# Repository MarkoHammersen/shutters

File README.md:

# ESP32 Shutter Control System
This project implements a **ESP32-based shutter control system** designed for controlling shutter motors via relays, with clear separation between hardware abstraction and business logic.
The system combines **ESP32**, **Microchip MCP23017 I/O expanders**, and **ULN2003A Darlington arrays**, and is implemented in **C++ using PlatformIO with the Arduino framework**.

---

## System Overview
The shutter system consists of:

* An **ESP32** as the central controller
* **MCP23017 I/O expanders** for scalable digital input and output via I²C
* **ULN2003A Darlington transistor arrays** for driving relay coils
* A dedicated **external 5 V power supply** for stable I/O operation

All safety-relevant design aspects (galvanic separation, flyback protection, low coil current) are explicitly addressed in the extern hardware design, which is not part of the schematics attached.

---

## Hardware Architecture

### Inputs (Buttons / Wall Switches)

* Digital inputs are handled by an **MCP23017 configured as input expander**
* Button **press and release events** are captured
* Each input event triggers a **hardware interrupt**
* The interrupt line is connected to the ESP32
* Upon interrupt, the ESP32:

  1. Starts an I²C transaction
  2. Reads the MCP23017 input registers
  3. Determines the exact event (press or release)

This approach ensures:

* Low latency
* Minimal polling
* Efficient I²C bus usage

---

### Outputs (Shutter Actuation)

* Outputs are handled by a second **MCP23017 configured as output expander**
* Output states are sent from the ESP32 via **I²C**
* MCP23017 outputs drive **ULN2003A Darlington arrays**
* The Darlington arrays drive the **relay coils**

#### Relay Driving

* Relay coil current is low enough to be **safely driven by ULN2003A**
* **Flyback diodes** are mounted directly at the relay coils
* This protects the Darlington arrays and improves EMC robustness

> ⚠️ **Note:** Mains voltage must only be handled by qualified personnel.
---

### Power Supply

* All MCP23017 inputs and outputs are powered by a **stable external 5 V supply**
* This ensures:

  * Reliable logic levels
  * Noise immunity
  * Stable operation independent of ESP32 load conditions

---

## Software Architecture

The firmware is written in **C++** and built using:

* **PlatformIO**
* **Arduino framework**
* **ESP32 target**

The software is cleanly structured into three main layers using dedicated FreeRTOS tasks. The communication between these tasks are done via message queues:

### 1. Sensors

* Abstraction of all input devices
* MCP23017 input handling
* Interrupt processing
* Debouncing and event detection (press / release)

### 2. Actuators

* Abstraction of all output devices
* MCP23017 output handling
* Relay control logic
* Hardware-independent actuator interface

### 3. Shutter Business Logic

* High-level shutter control logic
* Direction handling (up / down)
* Timing and safety constraints
* Mutual exclusion of motor directions

#### State Machine

The business logic is implemented using a **state machine** based on:

👉 **Quantum Leaps – State-Oriented Programming**
[https://github.com/QuantumLeaps/State-Oriented-Programming](https://github.com/QuantumLeaps/State-Oriented-Programming)

This provides:

* Explicit, deterministic state handling
* Clear separation of states and events
* Improved maintainability and testability
* Robust behavior for asynchronous events (buttons, interrupts)

---

## Documentation & Schematics

* Hardware schematics are included in the repository

---

## Key Features

* ESP32-based central control
* Interrupt-driven input handling
* Scalable I/O via MCP23017
* Safe relay driving using ULN2003A
* Clear separation of concerns in software
* State-machine-driven business logic

---
### ⚠️ WARNING

This project uses electromechanical actuators.
Improper handling can result in serious injury, fire, or death.

This project is provided for educational and experimental purposes only.
The author assumes no liability for any damage, injury, or loss resulting
from the use, misuse, or modification of this hardware or software.

Only qualified personnel should work with mains voltage systems.

---
This project is not certified for commercial or residential use.
No compliance with CE, VDE, UL, or any other safety standard is claimed.
--
Use at your own risk!

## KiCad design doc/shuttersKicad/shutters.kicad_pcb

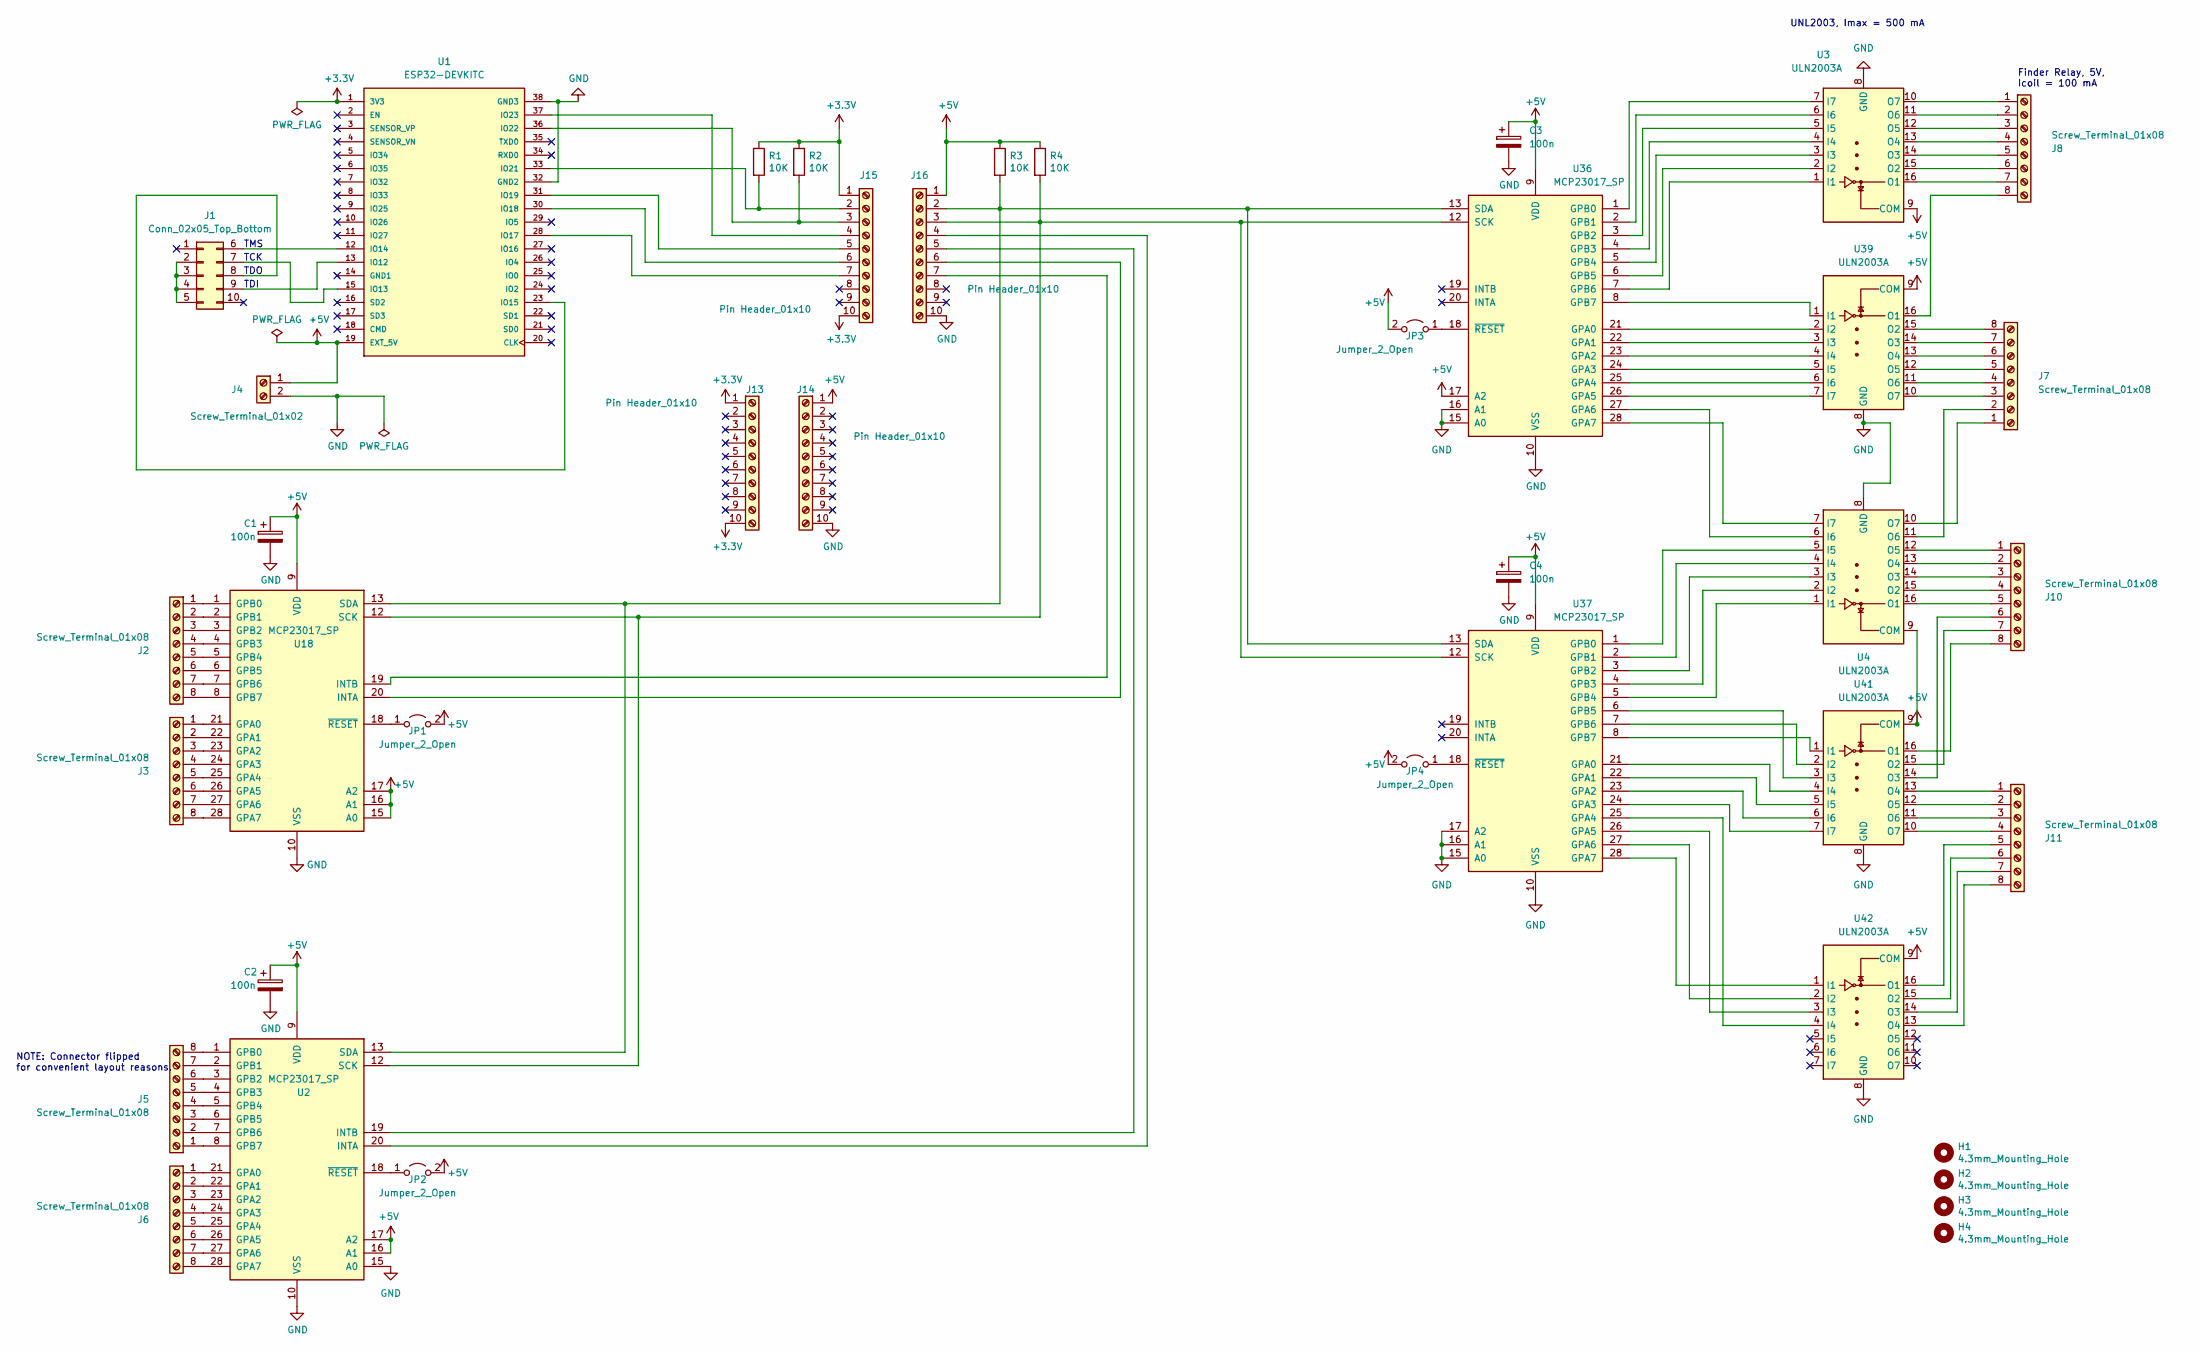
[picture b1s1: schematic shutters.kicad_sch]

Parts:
C1, C2, C3, C4: 100n; C_Rect_L7.0mm_W2.5mm_P5.00mm
H1, H2, H3, H4: 4.3mm_Mounting_Hole; MountingHole_4.3mm_M4
J1: Conn_02x05_Top_Bottom; PinHeader_2x05_P2.54mm_Vertical
J2, J3, J5, J6, J7, J8, J10, J11: Screw_Terminal_01x08; TerminalBlock_Phoenix_MKDS-1,5-8-5.08_1x08_P5.08mm_Horizont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
J4: Screw_Terminal_01x02; TerminalBlock_Phoenix_MKDS-1,5-2-5.08_1x02_P5.08mm_Horizont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
J13, J14, J15, J16: Pin Header_01x10; PinHeader_1x10_P2.54mm_Vertical
JP1, JP2, JP3, JP4: Jumper_2_Open; PinHeader_1x02_P2.54mm_Vertical
R1, R2, R3, R4: 10K; R_Axial_DIN0204_L3.6mm_D1.6mm_P5.08mm_Horizontal
U1: ESP32-DEVKITC; MODULE_ESP32-DEVKITC; PARTREV N/A
U2, U18, U36, U37: MCP23017_SP; DIP-28_W7.62mm
U3, U4, U39, U41, U42: ULN2003A; DIP-16_W7.62mm_Socket

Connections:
+3V3: J13.1, J13.10, J15.1, J15.10, R1.1, R2.1, U1.1 (3V3)
+5V: C1.1, C2.1, C3.1, C4.1, J4.1, J14.1, J16.1, JP1.2 (B), JP2.2 (B), JP3.2 (B), JP4.2 (B), R3.1, R4.1, U1.19 (EXT_5V), U2.9 (VDD), U2.16 (A1), U2.17 (A2), U3.9 (COM), U4.9 (COM), U18.9 (VDD), U18.15 (A0), U18.16 (A1), U18.17 (A2), U36.9 (VDD), U36.17 (A2), U37.9 (VDD), U39.9 (COM), U41.9 (COM), U42.9 (COM)
GND: C1.2, C2.2, C3.2, C4.2, J4.2, J14.10, J16.10, U1.32 (GND2), U1.38 (GND3), U2.10 (VSS), U2.15 (A0), U3.8 (GND), U4.8 (GND), U18.10 (VSS), U36.10 (VSS), U36.15 (A0), U36.16 (A1), U37.10 (VSS), U37.15 (A0), U37.16 (A1), U37.17 (A2), U39.8 (GND), U41.8 (GND), U42.8 (GND)
unnamed: J1.2, J1.3, J1.4, J1.5
unnamed: J1.6, U1.12 (IO14)
unnamed: J1.7, U1.15 (IO13)
unnamed: J1.8, U1.23 (IO15)
unnamed: J1.9, U1.13 (IO12)
unnamed: J2.1, U18.1 (GPB0)
unnamed: J2.2, U18.2 (GPB1)
unnamed: J2.3, U18.3 (GPB2)
unnamed: J2.4, U18.4 (GPB3)
unnamed: J2.5, U18.5 (GPB4)
unnamed: J2.6, U18.6 (GPB5)
unnamed: J2.7, U18.7 (GPB6)
unnamed: J2.8, U18.8 (GPB7)
unnamed: J3.1, U18.21 (GPA0)
unnamed: J3.2, U18.22 (GPA1)
unnamed: J3.3, U18.23 (GPA2)
unnamed: J3.4, U18.24 (GPA3)
unnamed: J3.5, U18.25 (GPA4)
unnamed: J3.6, U18.26 (GPA5)
unnamed: J3.7, U18.27 (GPA6)
unnamed: J3.8, U18.28 (GPA7)
unnamed: J5.1, U2.8 (GPB7)
unnamed: J5.2, U2.7 (GPB6)
unnamed: J5.3, U2.6 (GPB5)
unnamed: J5.4, U2.5 (GPB4)
unnamed: J5.5, U2.4 (GPB3)
unnamed: J5.6, U2.3 (GPB2)
unnamed: J5.7, U2.2 (GPB1)
unnamed: J5.8, U2.1 (GPB0)
unnamed: J6.1, U2.21 (GPA0)
unnamed: J6.2, U2.22 (GPA1)
unnamed: J6.3, U2.23 (GPA2)
unnamed: J6.4, U2.24 (GPA3)
unnamed: J6.5, U2.25 (GPA4)
unnamed: J6.6, U2.26 (GPA5)
unnamed: J6.7, U2.27 (GPA6)
unnamed: J6.8, U2.28 (GPA7)
unnamed: J7.1, U4.10 (O7)
unnamed: J7.2, U4.11 (O6)
unnamed: J7.3, U39.10 (O7)
unnamed: J7.4, U39.11 (O6)
unnamed: J7.5, U39.12 (O5)
unnamed: J7.6, U39.13 (O4)
unnamed: J7.7, U39.14 (O3)
unnamed: J7.8, U39.15 (O2)
unnamed: J8.1, U3.10 (O7)
unnamed: J8.2, U3.11 (O6)
unnamed: J8.3, U3.12 (O5)
unnamed: J8.4, U3.13 (O4)
unnamed: J8.5, U3.14 (O3)
unnamed: J8.6, U3.15 (O2)
unnamed: J8.7, U3.16 (O1)
unnamed: J8.8, U39.16 (O1)
unnamed: J10.1, U4.12 (O5)
unnamed: J10.2, U4.13 (O4)
unnamed: J10.3, U4.14 (O3)
unnamed: J10.4, U4.15 (O2)
unnamed: J10.5, U4.16 (O1)
unnamed: J10.6, U41.14 (O3)
unnamed: J10.7, U41.15 (O2)
unnamed: J10.8, U41.16 (O1)
unnamed: J11.1, U41.13 (O4)
unnamed: J11.2, U41.12 (O5)
unnamed: J11.3, U41.11 (O6)
unnamed: J11.4, U41.10 (O7)
unnamed: J11.5, U42.16 (O1)
unnamed: J11.6, U42.15 (O2)
unnamed: J11.7, U42.14 (O3)
unnamed: J11.8, U42.13 (O4)
unnamed: J15.2, R1.2, U1.33 (IO21)
unnamed: J15.3, R2.2, U1.36 (IO22)
unnamed: J15.4, U1.37 (IO23)
unnamed: J15.5, U1.31 (IO19)
unnamed: J15.6, U1.30 (IO18)
unnamed: J15.7, U1.28 (IO17)
unnamed: J16.2, R3.2, U2.13 (SDA), U18.13 (SDA), U36.13 (SDA), U37.13 (SDA)
unnamed: J16.3, R4.2, U2.12 (SCK), U18.12 (SCK), U36.12 (SCK), U37.12 (SCK)
unnamed: J16.4, U2.20 (INTA)
unnamed: J16.5, U2.19 (INTB)
unnamed: J16.6, U18.20 (INTA)
unnamed: J16.7, U18.19 (INTB)
unnamed: JP1.1 (A), U18.18 (~RESET)
unnamed: JP2.1 (A), U2.18 (~RESET)
unnamed: JP3.1 (A), U36.18 (~RESET)
unnamed: JP4.1 (A), U37.18 (~RESET)
unnamed: U3.1 (I1), U36.7 (GPB6)
unnamed: U3.2 (I2), U36.6 (GPB5)
unnamed: U3.3 (I3), U36.5 (GPB4)
unnamed: U3.4 (I4), U36.4 (GPB3)
unnamed: U3.5 (I5), U36.3 (GPB2)
unnamed: U3.6 (I6), U36.2 (GPB1)
unnamed: U3.7 (I7), U36.1 (GPB0)
unnamed: U36.8 (GPB7), U39.1 (I1)
unnamed: U36.21 (GPA0), U39.2 (I2)
unnamed: U36.22 (GPA1), U39.3 (I3)
unnamed: U36.23 (GPA2), U39.4 (I4)
unnamed: U36.24 (GPA3), U39.5 (I5)
unnamed: U36.25 (GPA4), U39.6 (I6)
unnamed: U36.26 (GPA5), U39.7 (I7)
unnamed: U4.6 (I6), U36.27 (GPA6)
unnamed: U4.7 (I7), U36.28 (GPA7)
unnamed: U4.5 (I5), U37.1 (GPB0)
unnamed: U4.4 (I4), U37.2 (GPB1)
unnamed: U4.3 (I3), U37.3 (GPB2)
unnamed: U4.2 (I2), U37.4 (GPB3)
unnamed: U4.1 (I1), U37.5 (GPB4)
unnamed: U37.6 (GPB5), U41.3 (I3)
unnamed: U37.7 (GPB6), U41.2 (I2)
unnamed: U37.8 (GPB7), U41.1 (I1)
unnamed: U37.21 (GPA0), U41.4 (I4)
unnamed: U37.22 (GPA1), U41.5 (I5)
unnamed: U37.23 (GPA2), U41.6 (I6)
unnamed: U37.24 (GPA3), U41.7 (I7)
unnamed: U37.25 (GPA4), U42.4 (I4)
unnamed: U37.26 (GPA5), U42.3 (I3)
unnamed: U37.27 (GPA6), U42.2 (I2)
unnamed: U37.28 (GPA7), U42.1 (I1)

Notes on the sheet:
UNL2003, Imax = 500 mA
Finder Relay, 5V, Icoil = 100 mA
TMS
TCK
TDO
NOTE: Connector flipped for convenient layout reasons.
TDI

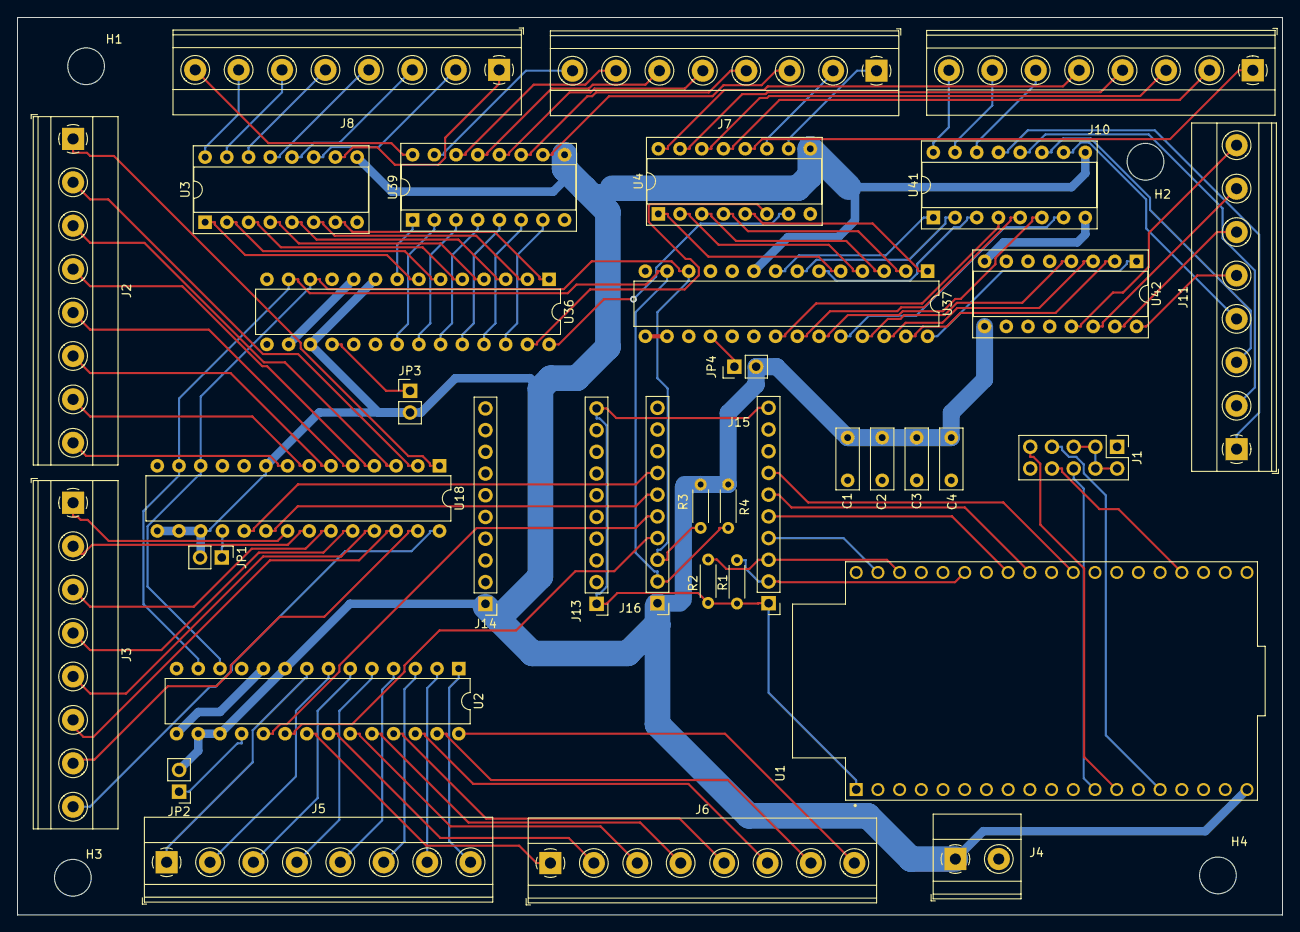
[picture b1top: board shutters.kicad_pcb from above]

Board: 2 copper layers, 148.0 x 105.0 mm, 40 parts (0 on the bottom side), 120 nets.

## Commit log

2023-10-15 initial version
2023-10-15 schematics
2023-10-16 remove hsm as local files
2023-10-16 next
2023-10-18 first version
2023-10-18 tests
2023-10-18 test
2023-10-19 critical section
2023-10-19 comments
2023-10-19 queues
2023-10-19 timers
2023-10-19 clean up
2023-10-20 unit tests shutters
2023-10-20 pin assignment
2023-10-26 format file
2023-10-26 edit kicad
2024-01-15 enable all windows
2024-01-15 configure pinout
2024-01-19 testd on HW
2024-01-20 Sensor reading and releasing complete
2024-01-20 tests of actuators ok
2024-01-21 update to Miro's lates hsm changes
2024-01-22 pin configuration
2024-01-22 time configuration
2026-02-03 Update README with project details and architecture
    Added detailed project description, system overview, hardware and software architecture, and key features for the ESP32 Shutter Control System.
2026-02-03 Revise README for clarity and safety warnings
    Updated project description and added warning about electromechanical actuators and safety compliance.
2026-02-03 Update LICENSE
2026-02-03 Update README to clarify software structure
    Clarified the description of the software structure to include FreeRTOS tasks and message queues.
